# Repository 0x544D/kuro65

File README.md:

# Kuro65

The hot-swappable ISO mechanical keyboard PCB. 

Features include:
- QMK compatible
- Hot-swappable MX sockets
- 65% ISO DE layout
- Per-key RGB LED
- Multi-layer support

### Table of contents
- [Schematic](#schematic)
- [Bill of Material](#bom)
- [Pictures](#pictures)

# Schematic
<a name="schematic"/>
Standard schematic for a QMK firmware compatible mechanical keyboard.

#### Main schematic:

#### Switch matrix schematic:

# Bill of Material
<a name="bom"/>

| Qty | Component       | Footprint      | JLC Part Number | Datasheet | Shop URL                                                                 |
|-----|-----------------|----------------|-----------------|-----------|--------------------------------------------------------------------------|
|  1  | ATMEGA32U4-MU   | QFN-44_7x7x05P | C112161         |[Datasheet](https://datasheet.lcsc.com/lcsc/1809032024_Microchip-Tech-ATMEGA32U4-MU_C112161.pdf) | [Link](https://jlcpcb.com/partdetail/MicrochipTech-ATMEGA32U4MU/C112161) |
|  1  | X322516MLB4SI   | SMD3225-4P     | C13738          |[Datasheet](https://datasheet.lcsc.com/lcsc/2103291133_Yangxing-Tech-X322516MLB4SI_C13738.pdf) | [Link](https://jlcpcb.com/partdetail/YangxingTech-X322516MLB4SI/C13738) |
|  1  | B3FS-1000P      | SMD,6x6x3.1mm  | C271750         |[Datasheet](https://omronfs.omron.com/en_US/ecb/products/pdf/en-b3fs.pdf) | [Link](https://jlcpcb.com/partdetail/OmronElectronics-B3FS1000P/C271750) |
|  1  | TYPE-C-31-M-12  | SMD            | C165948         |[Datasheet](https://datasheet.lcsc.com/lcsc/2205251630_Korean-Hroparts-Elec-TYPE-C-31-M-12_C165948.pdf) | [Link](https://jlcpcb.com/partdetail/Korean_HropartsElec-TYPE_C_31_M12/C165948) |
| 70  | CPG151101S11    | SMD            | C2803348        |[Datasheet](https://datasheet.lcsc.com/lcsc/2202281830_Kailh-CPG151101S11_C2803348.pdf) | [Link](https://jlcpcb.com/partdetail/Kailh-CPG151101S11/C2803348) |
| 70  | 1N4148W         | SOD-123        | C109203         |[Datasheet](https://datasheet.lcsc.com/lcsc/1811131721_Shikues-1N4148W_C109203.pdf) | [Link](https://jlcpcb.com/partdetail/Shikues-1N4148W/C109203) |

# Pictures
<a name="pictures"/>

Kuro65 PCB

Kuro65 inside TOFU65 case

# Contributors and Acknowledgements
- Keyswitches based on: [daprice](https://github.com/daprice/keyswitches.pretty)
- Stabilizers used: [perigoso](https://github.com/perigoso/Switch_Keyboard)

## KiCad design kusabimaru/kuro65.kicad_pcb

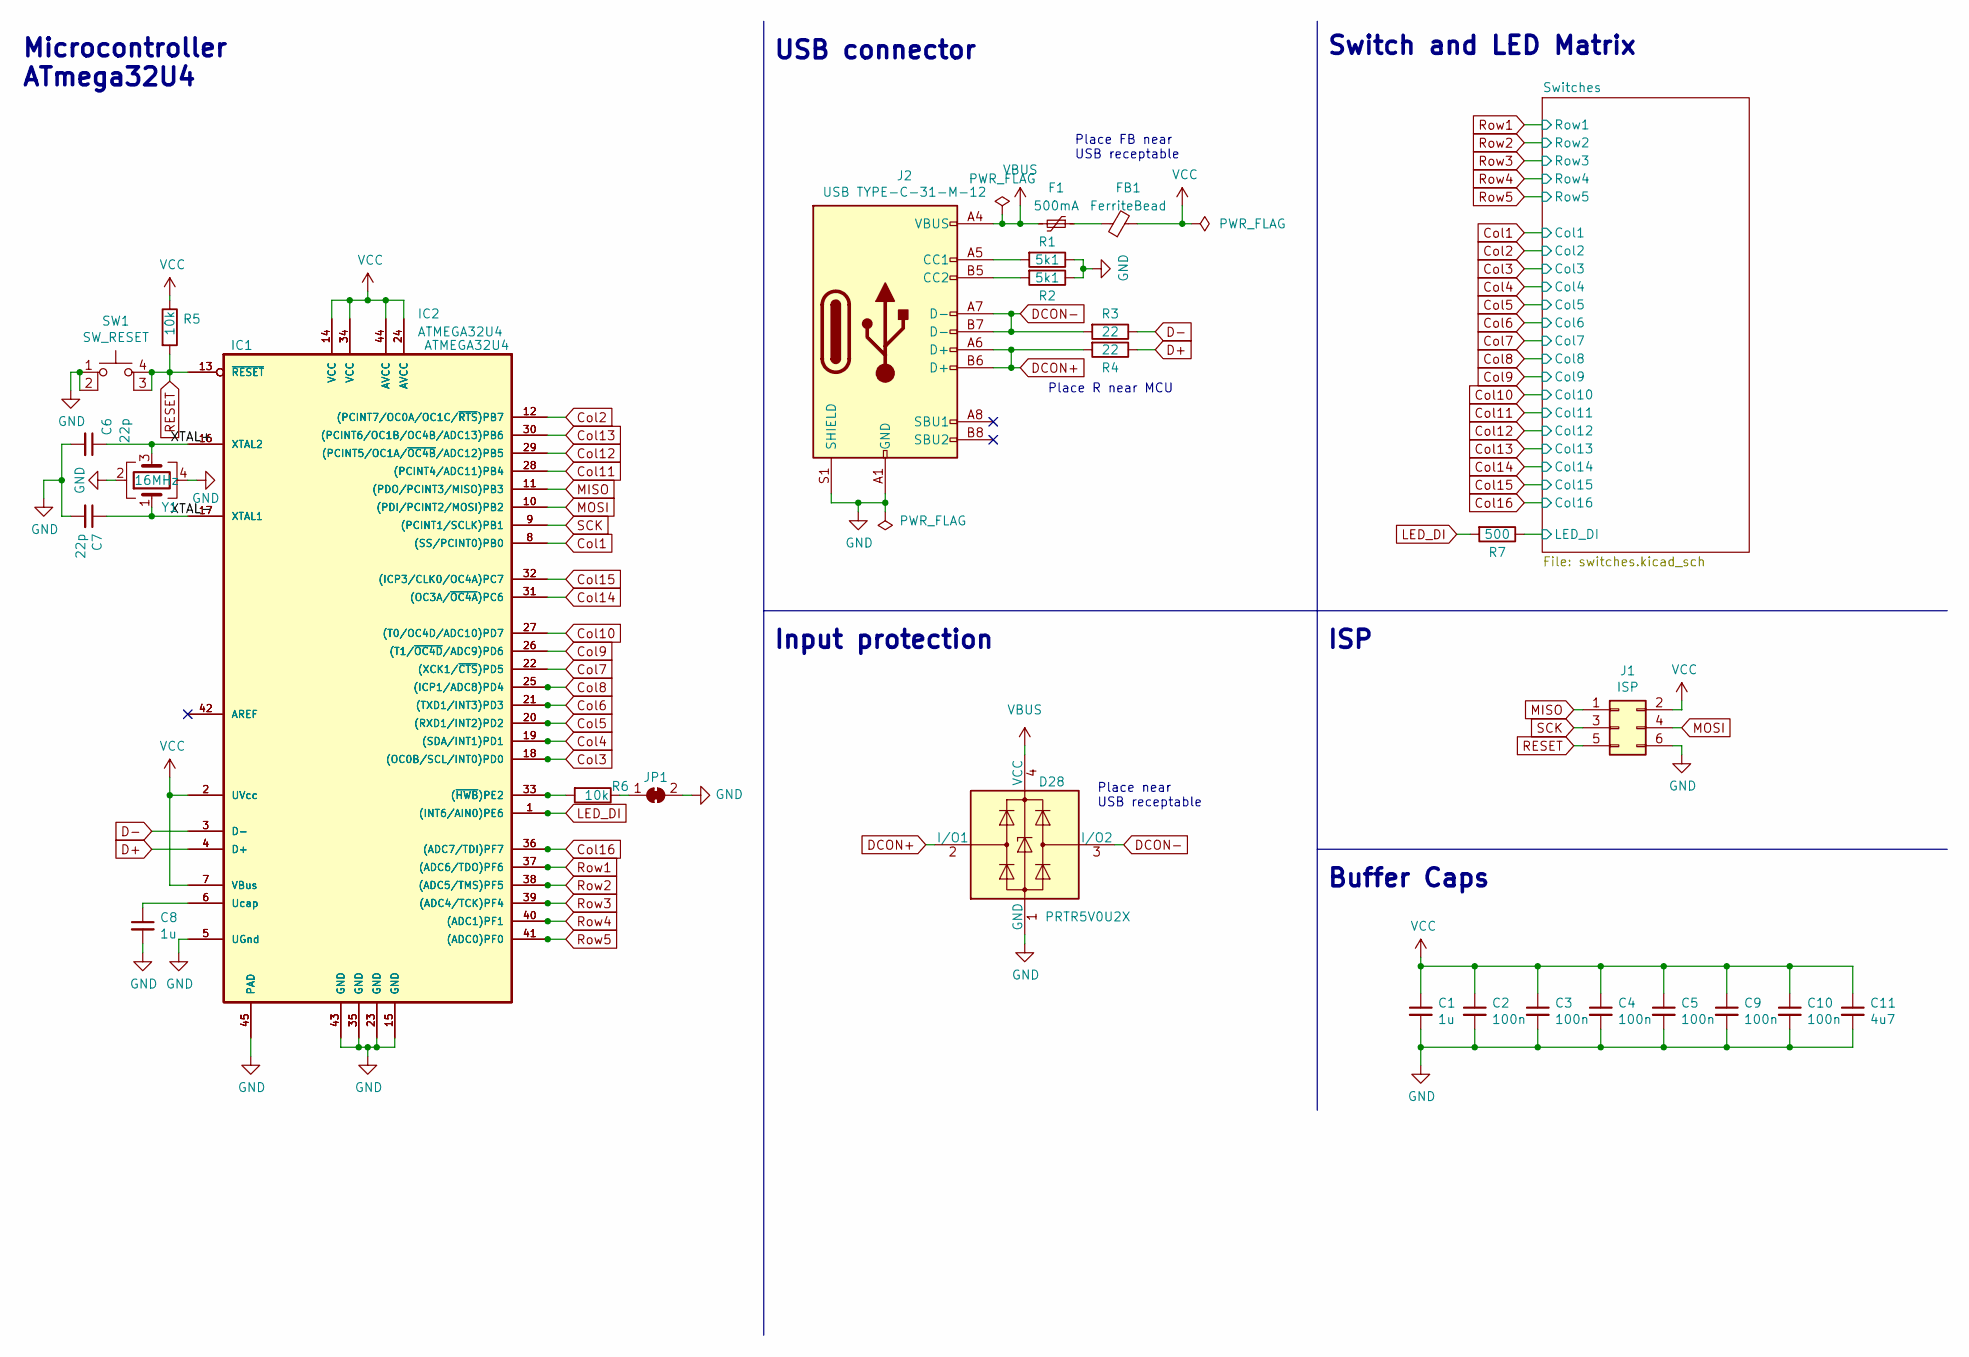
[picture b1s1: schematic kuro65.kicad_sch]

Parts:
C1, C8: 1u; C_0603_1608Metric_Pad1.08x0.95mm_HandSolder
C2, C3, C4, C5, C9, C10: 100n; C_0603_1608Metric_Pad1.08x0.95mm_HandSolder
C6, C7: 22p; C_0603_1608Metric_Pad1.08x0.95mm_HandSolder
C11: 4u7; C_0603_1608Metric_Pad1.08x0.95mm_HandSolder
D28: PRTR5V0U2X; SOT-143
F1: 500mA; Fuse_0603_1608Metric_Pad1.05x0.95mm_HandSolder
FB1: FerriteBead; R_0805_2012Metric_Pad1.20x1.40mm_HandSolder
IC1: ATMEGA32U4; QFN-44-1EP_7x7mm_P0.5mm_EP5.2x5.2mm_ThermalVias
IC2: ATMEGA32U4; LQFP-44_10x10mm_P0.8mm
J1: ISP; PinHeader_2x03_P2.54mm_Vertical
J2: USB TYPE-C-31-M-12; USB_C_Receptacle_HRO_TYPE-C-31-M-12
JP1: SolderJumper_2_Bridged; SolderJumper-2_P1.3mm_Open_Pad1.0x1.5mm
R1, R2: 5k1; R_0603_1608Metric_Pad0.98x0.95mm_HandSolder
R3, R4: 22; R_0603_1608Metric_Pad0.98x0.95mm_HandSolder
R5, R6: 10k; R_0603_1608Metric_Pad0.98x0.95mm_HandSolder
R7: 500; R_0603_1608Metric_Pad0.98x0.95mm_HandSolder
SW1: SW_RESET; SW_SPST_Omron_B3FS-100xP
Y1: 16MHz; Crystal_SMD_SeikoEpson_TSX3225-4Pin_3.2x2.5mm_HandSoldering

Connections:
/Switches/LED_DI: R7.1; also elsewhere on the board
/XTAL+: C6.1, IC1.16 (XTAL2), IC2.16 (XTAL2), Y1.3
/XTAL-: C7.1, IC1.17 (XTAL1), IC2.17 (XTAL1), Y1.1
Col1: IC1.8 ((SS/PCINT0)PB0), IC2.8 ((SS/PCINT0)PB0); also elsewhere on the board
Col2: IC1.12 ((PCINT7/OC0A/OC1C/~RTS)PB7), IC2.12 ((PCINT7/OC0A/OC1C/~RTS)PB7); also elsewhere on the board
Col3: IC1.18 ((OC0B/SCL/INT0)PD0), IC2.18 ((OC0B/SCL/INT0)PD0); also elsewhere on the board
Col4: IC1.19 ((SDA/INT1)PD1), IC2.19 ((SDA/INT1)PD1); also elsewhere on the board
Col5: IC1.20 ((RXD1/INT2)PD2), IC2.20 ((RXD1/INT2)PD2); also elsewhere on the board
Col6: IC1.21 ((TXD1/INT3)PD3), IC2.21 ((TXD1/INT3)PD3); also elsewhere on the board
Col7: IC1.22 ((XCK1/~CTS)PD5), IC2.22 ((XCK1/~CTS)PD5); also elsewhere on the board
Col8: IC1.25 ((ICP1/ADC8)PD4), IC2.25 ((ICP1/ADC8)PD4); also elsewhere on the board
Col9: IC1.26 ((T1/~OC4D/ADC9)PD6), IC2.26 ((T1/~OC4D/ADC9)PD6); also elsewhere on the board
Col10: IC1.27 ((T0/OC4D/ADC10)PD7), IC2.27 ((T0/OC4D/ADC10)PD7); also elsewhere on the board
Col11: IC1.28 ((PCINT4/ADC11)PB4), IC2.28 ((PCINT4/ADC11)PB4); also elsewhere on the board
Col12: IC1.29 ((PCINT5/OC1A/~OC4B/ADC12)PB5), IC2.29 ((PCINT5/OC1A/~OC4B/ADC12)PB5); also elsewhere on the board
Col13: IC1.30 ((PCINT6/OC1B/OC4B/ADC13)PB6), IC2.30 ((PCINT6/OC1B/OC4B/ADC13)PB6); also elsewhere on the board
Col14: IC1.31 ((OC3A/~OC4A)PC6), IC2.31 ((OC3A/~OC4A)PC6); also elsewhere on the board
Col15: IC1.32 ((ICP3/CLK0/OC4A)PC7), IC2.32 ((ICP3/CLK0/OC4A)PC7); also elsewhere on the board
Col16: IC1.36 ((ADC7/TDI)PF7), IC2.36 ((ADC7/TDI)PF7); also elsewhere on the board
D+: IC1.4 (D+), IC2.4 (D+), R4.1
D-: IC1.3 (D-), IC2.3 (D-), R3.1
DCON+: D28.2 (I/O1), J2.A6 (D+), J2.B6 (D+), R4.2
DCON-: D28.3 (I/O2), J2.A7 (D-), J2.B7 (D-), R3.2
GND: C1.2, C2.2, C3.2, C4.2, C5.2, C6.2, C7.2, C8.2, C9.2, C10.2, C11.2, D28.1 (GND), IC1.5 (UGnd), IC1.15 (GND), IC1.23 (GND), IC1.35 (GND), IC1.43 (GND), IC1.45 (PAD), IC2.5 (UGnd), IC2.15 (GND), IC2.23 (GND), IC2.35 (GND), IC2.43 (GND), IC2.45 (PAD), J1.6, J2.A1 (GND), J2.A12 (GND), J2.B1 (GND), J2.B12 (GND), J2.S1 (SHIELD), JP1.2 (B), R1.1, R2.1, SW1.1, SW1.2, Y1.2, Y1.4; also elsewhere on the board
LED_DI: IC1.1 ((INT6/AIN0)PE6), IC2.1 ((INT6/AIN0)PE6), R7.2
MISO: IC1.11 ((PDO/PCINT3/MISO)PB3), IC2.11 ((PDO/PCINT3/MISO)PB3), J1.1
MOSI: IC1.10 ((PDI/PCINT2/MOSI)PB2), IC2.10 ((PDI/PCINT2/MOSI)PB2), J1.4
unnamed: C8.1, IC1.6 (Ucap), IC2.6 (Ucap)
unnamed: F1.1, FB1.1
unnamed: IC1.33 ((~HWB)PE2), IC2.33 ((~HWB)PE2), R6.2
unnamed: J2.A5 (CC1), R1.2
unnamed: J2.B5 (CC2), R2.2
unnamed: JP1.1 (A), R6.1
RESET: IC1.13 (~RESET), IC2.13 (~RESET), J1.5, R5.2, SW1.3 (K), SW1.4 (A)
Row1: IC1.37 ((ADC6/TDO)PF6), IC2.37 ((ADC6/TDO)PF6); also elsewhere on the board
Row2: IC1.38 ((ADC5/TMS)PF5), IC2.38 ((ADC5/TMS)PF5); also elsewhere on the board
Row3: IC1.39 ((ADC4/TCK)PF4), IC2.39 ((ADC4/TCK)PF4); also elsewhere on the board
Row4: IC1.40 ((ADC1)PF1), IC2.40 ((ADC1)PF1); also elsewhere on the board
Row5: IC1.41 ((ADC0)PF0), IC2.41 ((ADC0)PF0); also elsewhere on the board
SCK: IC1.9 ((PCINT1/SCLK)PB1), IC2.9 ((PCINT1/SCLK)PB1), J1.3
VBUS: D28.4 (VCC), F1.2, J2.A4 (VBUS), J2.A9 (VBUS), J2.B4 (VBUS), J2.B9 (VBUS)
VCC: C1.1, C2.1, C3.1, C4.1, C5.1, C9.1, C10.1, C11.1, FB1.2, IC1.2 (UVcc), IC1.7 (VBus), IC1.14 (VCC), IC1.24 (AVCC), IC1.34 (VCC), IC1.44 (AVCC), IC2.2 (UVcc), IC2.7 (VBus), IC2.14 (VCC), IC2.24 (AVCC), IC2.34 (VCC), IC2.44 (AVCC), J1.2, R5.1; also elsewhere on the board

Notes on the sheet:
Buffer Caps
USB connector
Place FB near USB receptable
Input protection
Place R near MCU
ISP
Switch and LED Matrix
Place near USB receptable
Microcontroller ATmega32U4

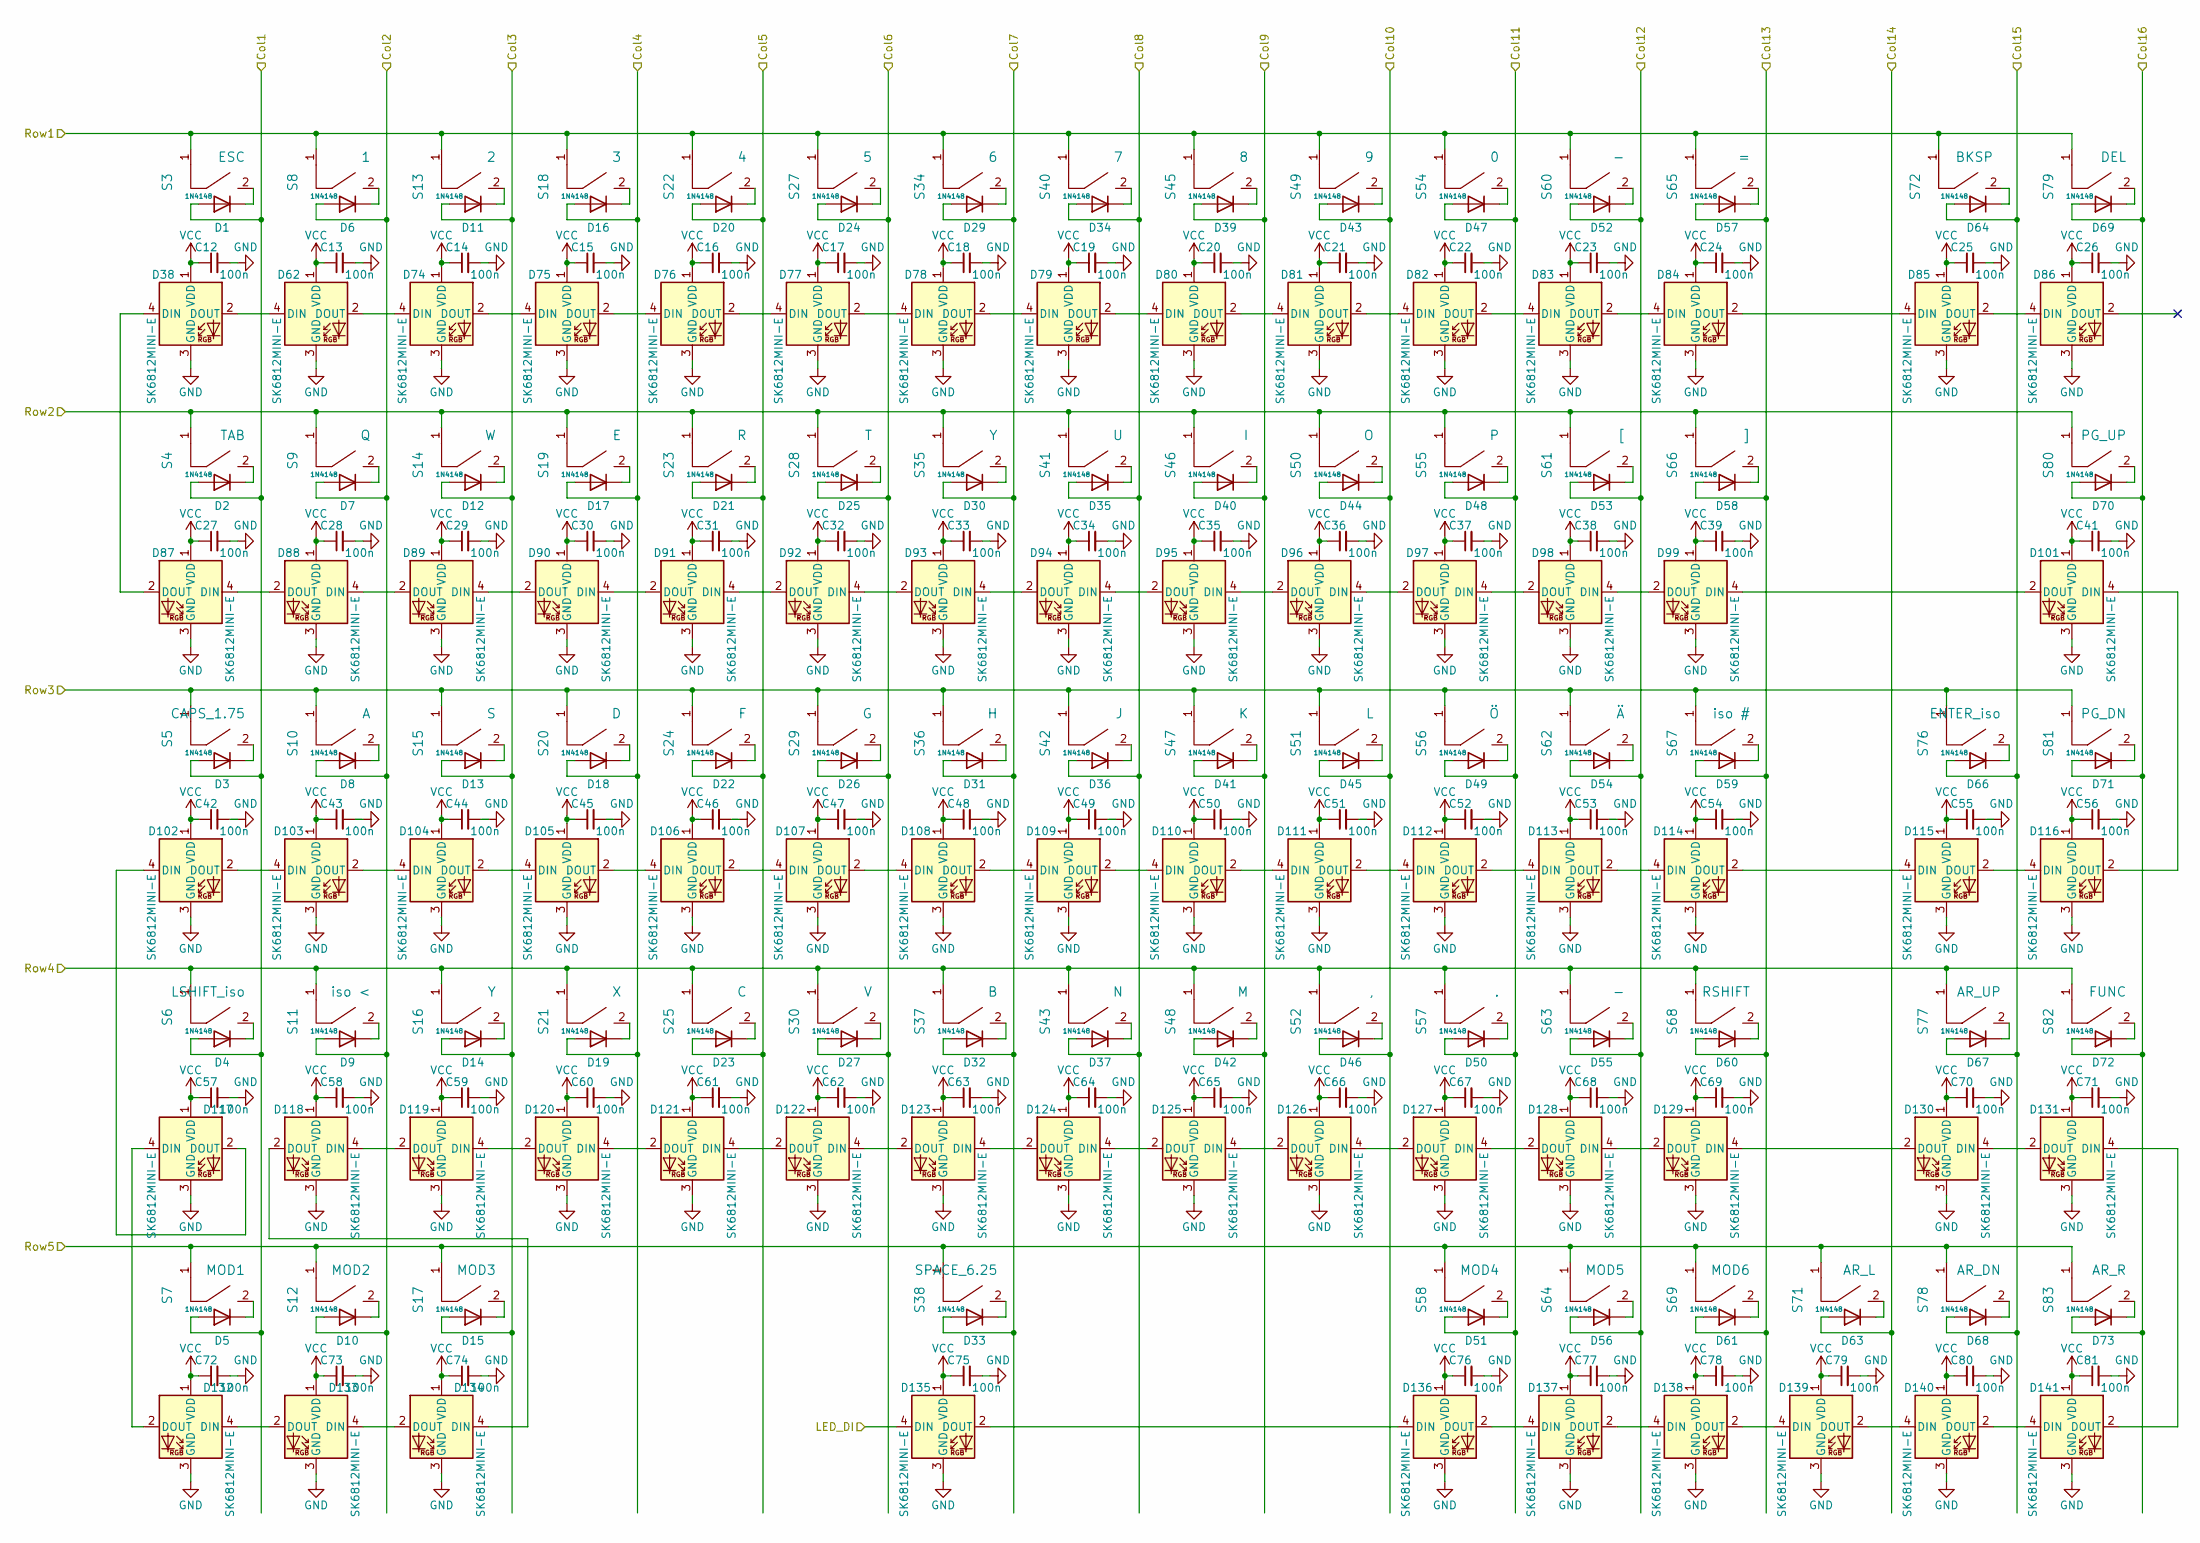
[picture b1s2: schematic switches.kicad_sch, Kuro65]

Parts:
C12, C13, C14, C15, C16, C17, C18, C19, C20, C21, C22, C23, C24, C25, C26, C27, C28, C29, C30, C31, C32, C33, C34, C35, C36, C37, C38, C39, C41, C42, C43, C44, C45, C46, C47, C48, C49, C50, C51, C52, C53, C54, C55, C56, C57, C58, C59, C60, C61, C62, C63, C64, C65, C66, C67, C68, C69, C70, C71, C72, C73, C74, C75, C76, C77, C78, C79, C80, C81: 100n; C_0603_1608Metric_Pad1.08x0.95mm_HandSolder
D1, D2, D3, D4, D5, D6, D7, D8, D9, D10, D11, D12, D13, D14, D15, D16, D17, D18, D19, D20, D21, D22, D23, D24, D25, D26, D27, D29, D30, D31, D32, D33, D34, D35, D36, D37, D39, D40, D41, D42, D43, D44, D45, D46, D47, D48, D49, D50, D51, D52, D53, D54, D55, D56, D57, D58, D59, D60, D61, D63, D64, D66, D67, D68, D69, D70, D71, D72, D73: 1N4148; D_SOD-123
D38, D62, D74, D75, D76, D77, D78, D79, D80, D81, D82, D83, D84, D85, D86, D87, D88, D89, D90, D91, D92, D93, D94, D95, D96, D97, D98, D99, D101, D102, D103, D104, D105, D106, D107, D108, D109, D110, D111, D112, D113, D114, D115, D116, D117, D118, D119, D120, D121, D122, D123, D124, D125, D126, D127, D128, D129, D130, D131, D132, D133, D134, D135, D136, D137, D138, D139, D140, D141: SK6812MINI-E; SK6812_MINI_E_small_cutout
S3: ESC; Kailh_socket_only_MX_smd_1u
S4: TAB; Kailh_socket_only_MX_smd_1.5u
S5: CAPS_1.75; Kailh_socket_only_MX_smd_1.75u
S6: LSHIFT_iso; Kailh_socket_only_MX_smd_1.25u
S7: MOD1; Kailh_socket_only_MX_smd_1.25u
S8: 1; Kailh_socket_only_MX_smd_1u
S9: Q; Kailh_socket_only_MX_smd_1u
S10: A; Kailh_socket_only_MX_smd_1u
S11: iso <; Kailh_socket_only_MX_smd_1u
S12: MOD2; Kailh_socket_only_MX_smd_1.25u
S13: 2; Kailh_socket_only_MX_smd_1u
S14: W; Kailh_socket_only_MX_smd_1u
S15: S; Kailh_socket_only_MX_smd_1u
S16, S35: Y; Kailh_socket_only_MX_smd_1u
S17: MOD3; Kailh_socket_only_MX_smd_1.25u
S18: 3; Kailh_socket_only_MX_smd_1u
S19: E; Kailh_socket_only_MX_smd_1u
S20: D; Kailh_socket_only_MX_smd_1u
S21: X; Kailh_socket_only_MX_smd_1u
S22: 4; Kailh_socket_only_MX_smd_1u
S23: R; Kailh_socket_only_MX_smd_1u
S24: F; Kailh_socket_only_MX_smd_1u
S25: C; Kailh_socket_only_MX_smd_1u
S27: 5; Kailh_socket_only_MX_smd_1u
S28: T; Kailh_socket_only_MX_smd_1u
S29: G; Kailh_socket_only_MX_smd_1u
S30: V; Kailh_socket_only_MX_smd_1u
S34: 6; Kailh_socket_only_MX_smd_1u
S36: H; Kailh_socket_only_MX_smd_1u
S37: B; Kailh_socket_only_MX_smd_1u
S38: SPACE_6.25; Kailh_socket_only_MX_smd_6.25u
S40: 7; Kailh_socket_only_MX_smd_1u
S41: U; Kailh_socket_only_MX_smd_1u
S42: J; Kailh_socket_only_MX_smd_1u
S43: N; Kailh_socket_only_MX_smd_1u
S45: 8; Kailh_socket_only_MX_smd_1u
S46: I; Kailh_socket_only_MX_smd_1u
S47: K; Kailh_socket_only_MX_smd_1u
S48: M; Kailh_socket_only_MX_smd_1u
S49: 9; Kailh_socket_only_MX_smd_1u
S50: O; Kailh_socket_only_MX_smd_1u
S51: L; Kailh_socket_only_MX_smd_1u
S52: ,; Kailh_socket_only_MX_smd_1u
S54: 0; Kailh_socket_only_MX_smd_1u
S55: P; Kailh_socket_only_MX_smd_1u
S56: Ö; Kailh_socket_only_MX_smd_1u
S57: .; Kailh_socket_only_MX_smd_1u
S58: MOD4; Kailh_socket_only_MX_smd_1u
S60, S63: -; Kailh_socket_only_MX_smd_1u
S61: [; Kailh_socket_only_MX_smd_1u
S62: Ä; Kailh_socket_only_MX_smd_1u
S64: MOD5; Kailh_socket_only_MX_smd_1u
S65: =; Kailh_socket_only_MX_smd_1u
S66: ]; Kailh_socket_only_MX_smd_1u
S67: iso #; Kailh_socket_only_MX_smd_1u
S68: RSHIFT; Kailh_socket_only_MX_smd_1.75u
S69: MOD6; Kailh_socket_only_MX_smd_1u
S71: AR_L; Kailh_socket_only_MX_smd_1u
S72: BKSP; Kailh_socket_only_MX_smd_2u
S76: ENTER_iso; Kailh_socket_only_MX_smd_iso_enter
S77: AR_UP; Kailh_socket_only_MX_smd_1u
S78: AR_DN; Kailh_socket_only_MX_smd_1u
S79: DEL; Kailh_socket_only_MX_smd_1u
S80: PG_UP; Kailh_socket_only_MX_smd_1u
S81: PG_DN; Kailh_socket_only_MX_smd_1u
S82: FUNC; Kailh_socket_only_MX_smd_1u
S83: AR_R; Kailh_socket_only_MX_smd_1u

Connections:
/Switches/LED_DI: D135.4 (DIN); also elsewhere on the board
Col1: D1.2 (A), D2.2 (A), D3.2 (A), D4.2 (A), D5.2 (A); also elsewhere on the board
Col2: D6.2 (A), D7.2 (A), D8.2 (A), D9.2 (A), D10.2 (A); also elsewhere on the board
Col3: D11.2 (A), D12.2 (A), D13.2 (A), D14.2 (A), D15.2 (A); also elsewhere on the board
Col4: D16.2 (A), D17.2 (A), D18.2 (A), D19.2 (A); also elsewhere on the board
Col5: D20.2 (A), D21.2 (A), D22.2 (A), D23.2 (A); also elsewhere on the board
Col6: D24.2 (A), D25.2 (A), D26.2 (A), D27.2 (A); also elsewhere on the board
Col7: D29.2 (A), D30.2 (A), D31.2 (A), D32.2 (A), D33.2 (A); also elsewhere on the board
Col8: D34.2 (A), D35.2 (A), D36.2 (A), D37.2 (A); also elsewhere on the board
Col9: D39.2 (A), D40.2 (A), D41.2 (A), D42.2 (A); also elsewhere on the board
Col10: D43.2 (A), D44.2 (A), D45.2 (A), D46.2 (A); also elsewhere on the board
Col11: D47.2 (A), D48.2 (A), D49.2 (A), D50.2 (A), D51.2 (A); also elsewhere on the board
Col12: D52.2 (A), D53.2 (A), D54.2 (A), D55.2 (A), D56.2 (A); also elsewhere on the board
Col13: D57.2 (A), D58.2 (A), D59.2 (A), D60.2 (A), D61.2 (A); also elsewhere on the board
Col14: D63.2 (A); also elsewhere on the board
Col15: D64.2 (A), D66.2 (A), D67.2 (A), D68.2 (A); also elsewhere on the board
Col16: D69.2 (A), D70.2 (A), D71.2 (A), D72.2 (A), D73.2 (A); also elsewhere on the board
GND: C12.2, C13.2, C14.2, C15.2, C16.2, C17.2, C18.2, C19.2, C20.2, C21.2, C22.2, C23.2, C24.2, C25.2, C26.2, C27.2, C28.2, C29.2, C30.2, C31.2, C32.2, C33.2, C34.2, C35.2, C36.2, C37.2, C38.2, C39.2, C41.2, C42.2, C43.2, C44.2, C45.2, C46.2, C47.2, C48.2, C49.2, C50.2, C51.2, C52.2, C53.2, C54.2, C55.2, C56.2, C57.2, C58.2, C59.2, C60.2, C61.2, C62.2, C63.2, C64.2, C65.2, C66.2, C67.2, C68.2, C69.2, C70.2, C71.2, C72.2, C73.2, C74.2, C75.2, C76.2, C77.2, C78.2, C79.2, C80.2, C81.2, D38.3 (GND), D62.3 (GND), D74.3 (GND), D75.3 (GND), D76.3 (GND), D77.3 (GND), D78.3 (GND), D79.3 (GND), D80.3 (GND), D81.3 (GND), D82.3 (GND), D83.3 (GND), D84.3 (GND), D85.3 (GND), D86.3 (GND), D87.3 (GND), D88.3 (GND), D89.3 (GND), D90.3 (GND), D91.3 (GND), D92.3 (GND), D93.3 (GND), D94.3 (GND), D95.3 (GND), D96.3 (GND), D97.3 (GND), D98.3 (GND), D99.3 (GND), D101.3 (GND), D102.3 (GND), D103.3 (GND), D104.3 (GND), D105.3 (GND), D106.3 (GND), D107.3 (GND), D108.3 (GND), D109.3 (GND), D110.3 (GND), D111.3 (GND), D112.3 (GND), D113.3 (GND), D114.3 (GND), D115.3 (GND), D116.3 (GND), D117.3 (GND), D118.3 (GND), D119.3 (GND), D120.3 (GND), D121.3 (GND), D122.3 (GND), D123.3 (GND), D124.3 (GND), D125.3 (GND), D126.3 (GND), D127.3 (GND), D128.3 (GND), D129.3 (GND), D130.3 (GND), D131.3 (GND), D132.3 (GND), D133.3 (GND), D134.3 (GND), D135.3 (GND), D136.3 (GND), D137.3 (GND), D138.3 (GND), D139.3 (GND), D140.3 (GND), D141.3 (GND); also elsewhere on the board
unnamed: D1.1 (K), S3.2
unnamed: D2.1 (K), S4.2
unnamed: D3.1 (K), S5.2
unnamed: D4.1 (K), S6.2
unnamed: D5.1 (K), S7.2
unnamed: D6.1 (K), S8.2
unnamed: D7.1 (K), S9.2
unnamed: D8.1 (K), S10.2
unnamed: D9.1 (K), S11.2
unnamed: D10.1 (K), S12.2
unnamed: D11.1 (K), S13.2
unnamed: D12.1 (K), S14.2
unnamed: D13.1 (K), S15.2
unnamed: D14.1 (K), S16.2
unnamed: D15.1 (K), S17.2
unnamed: D16.1 (K), S18.2
unnamed: D17.1 (K), S19.2
unnamed: D18.1 (K), S20.2
unnamed: D19.1 (K), S21.2
unnamed: D20.1 (K), S22.2
unnamed: D21.1 (K), S23.2
unnamed: D22.1 (K), S24.2
unnamed: D23.1 (K), S25.2
unnamed: D24.1 (K), S27.2
unnamed: D25.1 (K), S28.2
unnamed: D26.1 (K), S29.2
unnamed: D27.1 (K), S30.2
unnamed: D29.1 (K), S34.2
unnamed: D30.1 (K), S35.2
unnamed: D31.1 (K), S36.2
unnamed: D32.1 (K), S37.2
unnamed: D33.1 (K), S38.2
unnamed: D34.1 (K), S40.2
unnamed: D35.1 (K), S41.2
unnamed: D36.1 (K), S42.2
unnamed: D37.1 (K), S43.2
unnamed: D38.2 (DOUT), D62.4 (DIN)
unnamed: D39.1 (K), S45.2
unnamed: D40.1 (K), S46.2
unnamed: D41.1 (K), S47.2
unnamed: D42.1 (K), S48.2
unnamed: D43.1 (K), S49.2
unnamed: D44.1 (K), S50.2
unnamed: D45.1 (K), S51.2
unnamed: D46.1 (K), S52.2
unnamed: D47.1 (K), S54.2
unnamed: D48.1 (K), S55.2
unnamed: D49.1 (K), S56.2
unnamed: D50.1 (K), S57.2
unnamed: D51.1 (K), S58.2
unnamed: D52.1 (K), S60.2
unnamed: D53.1 (K), S61.2
unnamed: D54.1 (K), S62.2
unnamed: D55.1 (K), S63.2
unnamed: D56.1 (K), S64.2
unnamed: D57.1 (K), S65.2
unnamed: D58.1 (K), S66.2
unnamed: D59.1 (K), S67.2
unnamed: D60.1 (K), S68.2
unnamed: D61.1 (K), S69.2
unnamed: D62.2 (DOUT), D74.4 (DIN)
unnamed: D63.1 (K), S71.2
unnamed: D64.1 (K), S72.2
unnamed: D66.1 (K), S76.2
unnamed: D67.1 (K), S77.2
unnamed: D68.1 (K), S78.2
unnamed: D69.1 (K), S79.2
unnamed: D70.1 (K), S80.2
unnamed: D71.1 (K), S81.2
unnamed: D72.1 (K), S82.2
unnamed: D73.1 (K), S83.2
unnamed: D74.2 (DOUT), D75.4 (DIN)
unnamed: D75.2 (DOUT), D76.4 (DIN)
unnamed: D76.2 (DOUT), D77.4 (DIN)
unnamed: D77.2 (DOUT), D78.4 (DIN)
unnamed: D78.2 (DOUT), D79.4 (DIN)
unnamed: D79.2 (DOUT), D80.4 (DIN)
unnamed: D80.2 (DOUT), D81.4 (DIN)
unnamed: D81.2 (DOUT), D82.4 (DIN)
unnamed: D82.2 (DOUT), D83.4 (DIN)
unnamed: D83.2 (DOUT), D84.4 (DIN)
unnamed: D84.2 (DOUT), D85.4 (DIN)
unnamed: D85.2 (DOUT), D86.4 (DIN)
unnamed: D38.4 (DIN), D87.2 (DOUT)
unnamed: D87.4 (DIN), D88.2 (DOUT)
unnamed: D88.4 (DIN), D89.2 (DOUT)
unnamed: D89.4 (DIN), D90.2 (DOUT)
unnamed: D90.4 (DIN), D91.2 (DOUT)
unnamed: D91.4 (DIN), D92.2 (DOUT)
unnamed: D92.4 (DIN), D93.2 (DOUT)
unnamed: D93.4 (DIN), D94.2 (DOUT)
unnamed: D94.4 (DIN), D95.2 (DOUT)
unnamed: D95.4 (DIN), D96.2 (DOUT)
unnamed: D96.4 (DIN), D97.2 (DOUT)
unnamed: D97.4 (DIN), D98.2 (DOUT)
unnamed: D98.4 (DIN), D99.2 (DOUT)
unnamed: D99.4 (DIN), D101.2 (DOUT)
unnamed: D102.2 (DOUT), D103.4 (DIN)
unnamed: D102.4 (DIN), D117.2 (DOUT)
unnamed: D103.2 (DOUT), D104.4 (DIN)
unnamed: D104.2 (DOUT), D105.4 (DIN)
unnamed: D105.2 (DOUT), D106.4 (DIN)
unnamed: D106.2 (DOUT), D107.4 (DIN)
unnamed: D107.2 (DOUT), D108.4 (DIN)
unnamed: D108.2 (DOUT), D109.4 (DIN)
unnamed: D109.2 (DOUT), D110.4 (DIN)
unnamed: D110.2 (DOUT), D111.4 (DIN)
unnamed: D111.2 (DOUT), D112.4 (DIN)
unnamed: D112.2 (DOUT), D113.4 (DIN)
unnamed: D113.2 (DOUT), D114.4 (DIN)
unnamed: D114.2 (DOUT), D115.4 (DIN)
unnamed: D115.2 (DOUT), D116.4 (DIN)
unnamed: D101.4 (DIN), D116.2 (DOUT)
unnamed: D117.4 (DIN), D132.2 (DOUT)
unnamed: D118.2 (DOUT), D134.4 (DIN)
unnamed: D118.4 (DIN), D119.2 (DOUT)
unnamed: D119.4 (DIN), D120.2 (DOUT)
unnamed: D120.4 (DIN), D121.2 (DOUT)
unnamed: D121.4 (DIN), D122.2 (DOUT)
unnamed: D122.4 (DIN), D123.2 (DOUT)
unnamed: D123.4 (DIN), D124.2 (DOUT)
unnamed: D124.4 (DIN), D125.2 (DOUT)
unnamed: D125.4 (DIN), D126.2 (DOUT)
unnamed: D126.4 (DIN), D127.2 (DOUT)
unnamed: D127.4 (DIN), D128.2 (DOUT)
unnamed: D128.4 (DIN), D129.2 (DOUT)
unnamed: D129.4 (DIN), D130.2 (DOUT)
unnamed: D130.4 (DIN), D131.2 (DOUT)
unnamed: D131.4 (DIN), D141.2 (DOUT)
unnamed: D132.4 (DIN), D133.2 (DOUT)
unnamed: D133.4 (DIN), D134.2 (DOUT)
unnamed: D135.2 (DOUT), D136.4 (DIN)
unnamed: D136.2 (DOUT), D137.4 (DIN)
unnamed: D137.2 (DOUT), D138.4 (DIN)
unnamed: D138.2 (DOUT), D139.4 (DIN)
unnamed: D139.2 (DOUT), D140.4 (DIN)
unnamed: D140.2 (DOUT), D141.4 (DIN)
Row1: S3.1, S8.1, S13.1, S18.1, S22.1, S27.1, S34.1, S40.1, S45.1, S49.1, S54.1, S60.1, S65.1, S72.1, S79.1; also elsewhere on the board
Row2: S4.1, S9.1, S14.1, S19.1, S23.1, S28.1, S35.1, S41.1, S46.1, S50.1, S55.1, S61.1, S66.1, S80.1; also elsewhere on the board
Row3: S5.1, S10.1, S15.1, S20.1, S24.1, S29.1, S36.1, S42.1, S47.1, S51.1, S56.1, S62.1, S67.1, S76.1, S81.1; also elsewhere on the board
Row4: S6.1, S11.1, S16.1, S21.1, S25.1, S30.1, S37.1, S43.1, S48.1, S52.1, S57.1, S63.1, S68.1, S77.1, S82.1; also elsewhere on the board
Row5: S7.1, S12.1, S17.1, S38.1, S58.1, S64.1, S69.1, S71.1, S78.1, S83.1; also elsewhere on the board
VCC: C12.1, C13.1, C14.1, C15.1, C16.1, C17.1, C18.1, C19.1, C20.1, C21.1, C22.1, C23.1, C24.1, C25.1, C26.1, C27.1, C28.1, C29.1, C30.1, C31.1, C32.1, C33.1, C34.1, C35.1, C36.1, C37.1, C38.1, C39.1, C41.1, C42.1, C43.1, C44.1, C45.1, C46.1, C47.1, C48.1, C49.1, C50.1, C51.1, C52.1, C53.1, C54.1, C55.1, C56.1, C57.1, C58.1, C59.1, C60.1, C61.1, C62.1, C63.1, C64.1, C65.1, C66.1, C67.1, C68.1, C69.1, C70.1, C71.1, C72.1, C73.1, C74.1, C75.1, C76.1, C77.1, C78.1, C79.1, C80.1, C81.1, D38.1 (VDD), D62.1 (VDD), D74.1 (VDD), D75.1 (VDD), D76.1 (VDD), D77.1 (VDD), D78.1 (VDD), D79.1 (VDD), D80.1 (VDD), D81.1 (VDD), D82.1 (VDD), D83.1 (VDD), D84.1 (VDD), D85.1 (VDD), D86.1 (VDD), D87.1 (VDD), D88.1 (VDD), D89.1 (VDD), D90.1 (VDD), D91.1 (VDD), D92.1 (VDD), D93.1 (VDD), D94.1 (VDD), D95.1 (VDD), D96.1 (VDD), D97.1 (VDD), D98.1 (VDD), D99.1 (VDD), D101.1 (VDD), D102.1 (VDD), D103.1 (VDD), D104.1 (VDD), D105.1 (VDD), D106.1 (VDD), D107.1 (VDD), D108.1 (VDD), D109.1 (VDD), D110.1 (VDD), D111.1 (VDD), D112.1 (VDD), D113.1 (VDD), D114.1 (VDD), D115.1 (VDD), D116.1 (VDD), D117.1 (VDD), D118.1 (VDD), D119.1 (VDD), D120.1 (VDD), D121.1 (VDD), D122.1 (VDD), D123.1 (VDD), D124.1 (VDD), D125.1 (VDD), D126.1 (VDD), D127.1 (VDD), D128.1 (VDD), D129.1 (VDD), D130.1 (VDD), D131.1 (VDD), D132.1 (VDD), D133.1 (VDD), D134.1 (VDD), D135.1 (VDD), D136.1 (VDD), D137.1 (VDD), D138.1 (VDD), D139.1 (VDD), D140.1 (VDD), D141.1 (VDD); also elsewhere on the board

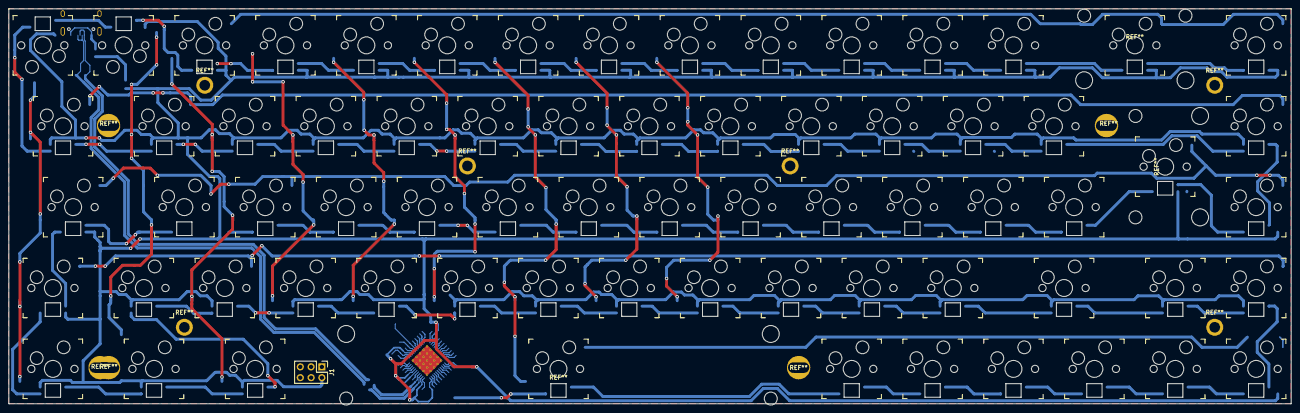
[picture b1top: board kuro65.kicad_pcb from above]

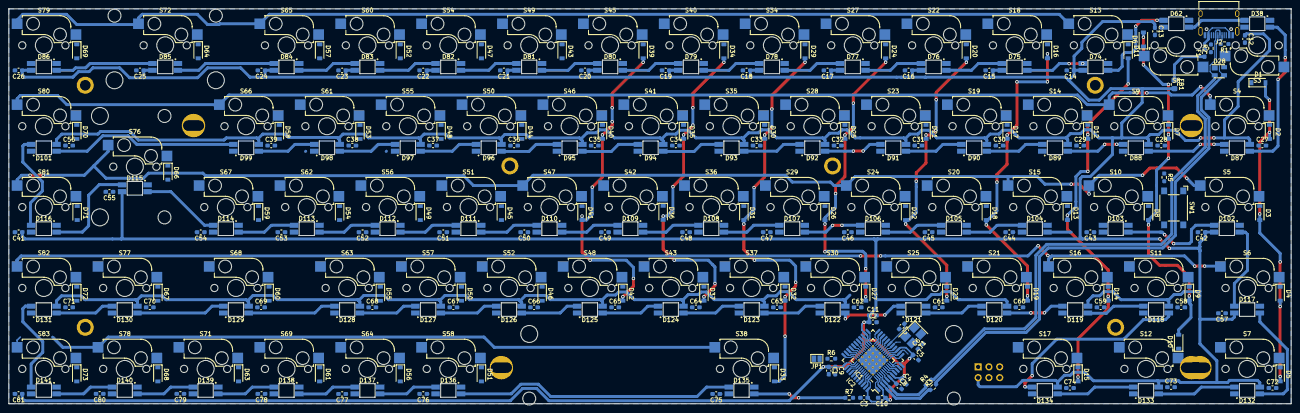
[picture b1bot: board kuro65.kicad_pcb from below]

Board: 2 copper layers, 302.0 x 93.0 mm, 304 parts (165 on the bottom side), 179 nets.

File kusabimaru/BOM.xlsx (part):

Source: | C:\Users\Tobi\Documents\GitHub\kuro65\kusabimaru\kuro65.sch
Date: | 44240.65384259259
Tool: | Eeschema (5.1.9)-1
Generator: | C:\Program Files\KiCad\bin\scripting\plugins/bom_csv_grouped_by_value.py
Component Count: | 171
Individual Components:
Item | Qty | Reference(s) | Value | LibPart | Footprint | Datasheet | Shop-URL
 |  | C1 | 1u | Device:C_Small | Capacitor_SMD:C_0805_2012Metric_Pad1.18x1.45mm_HandSolder | ~
 |  | C2 | 100n | Device:C_Small | Capacitor_SMD:C_0805_2012Metric_Pad1.18x1.45mm_HandSolder | ~
 |  | C3 | 100n | Device:C_Small | Capacitor_SMD:C_0805_2012Metric_Pad1.18x1.45mm_HandSolder | ~
 |  | C4 | 100n | Device:C_Small | Capacitor_SMD:C_0805_2012Metric_Pad1.18x1.45mm_HandSolder | ~
 |  | C5 | 100n | Device:C_Small | Capacitor_SMD:C_0805_2012Metric_Pad1.18x1.45mm_HandSolder | ~
 |  | C6 | 22p | Device:C_Small | Capacitor_SMD:C_0805_2012Metric_Pad1.18x1.45mm_HandSolder | ~
 |  | C7 | 22p | Device:C_Small | Capacitor_SMD:C_0805_2012Metric_Pad1.18x1.45mm_HandSolder | ~
 |  | C8 | 1u | Device:C_Small | Capacitor_SMD:C_0805_2012Metric_Pad1.18x1.45mm_HandSolder | ~
 |  | C9 | 100n | Device:C_Small | Capacitor_SMD:C_0805_2012Metric_Pad1.18x1.45mm_HandSolder | ~
 |  | C10 | 100n | Device:C_Small | Capacitor_SMD:C_0805_2012Metric_Pad1.18x1.45mm_HandSolder | ~
 |  | C11 | 4u7 | Device:C_Small | Capacitor_SMD:C_0805_2012Metric_Pad1.18x1.45mm_HandSolder | ~
 |  | D1 | 1N4148 | Device:D | Diode_SMD:D_0805_2012Metric_Pad1.15x1.40mm_HandSolder | ~
 |  | D2 | 1N4148 | Device:D | Diode_SMD:D_0805_2012Metric_Pad1.15x1.40mm_HandSolder | ~
 |  | D3 | 1N4148 | Device:D | Diode_SMD:D_0805_2012Metric_Pad1.15x1.40mm_HandSolder | ~
 |  | D4 | 1N4148 | Device:D | Diode_SMD:D_0805_2012Metric_Pad1.15x1.40mm_HandSolder | ~
 |  | D5 | 1N4148 | Device:D | Diode_SMD:D_0805_2012Metric_Pad1.15x1.40mm_HandSolder | ~
 |  | D6 | 1N4148 | Device:D | Diode_SMD:D_0805_2012Metric_Pad1.15x1.40mm_HandSolder | ~
 |  | D7 | 1N4148 | Device:D | Diode_SMD:D_0805_2012Metric_Pad1.15x1.40mm_HandSolder | ~
 |  | D8 | 1N4148 | Device:D | Diode_SMD:D_0805_2012Metric_Pad1.15x1.40mm_HandSolder | ~
 |  | D9 | 1N4148 | Device:D | Diode_SMD:D_0805_2012Metric_Pad1.15x1.40mm_HandSolder | ~
 |  | D10 | 1N4148 | Device:D | Diode_SMD:D_0805_2012Metric_Pad1.15x1.40mm_HandSolder | ~
 |  | D11 | 1N4148 | Device:D | Diode_SMD:D_0805_2012Metric_Pad1.15x1.40mm_HandSolder | ~
 |  | D12 | 1N4148 | Device:D | Diode_SMD:D_0805_2012Metric_Pad1.15x1.40mm_HandSolder | ~
 |  | D13 | 1N4148 | Device:D | Diode_SMD:D_0805_2012Metric_Pad1.15x1.40mm_HandSolder | ~
 |  | D14 | 1N4148 | Device:D | Diode_SMD:D_0805_2012Metric_Pad1.15x1.40mm_HandSolder | ~
 |  | D15 | 1N4148 | Device:D | Diode_SMD:D_0805_2012Metric_Pad1.15x1.40mm_HandSolder | ~
 |  | D16 | 1N4148 | Device:D | Diode_SMD:D_0805_2012Metric_Pad1.15x1.40mm_HandSolder | ~
 |  | D17 | 1N4148 | Device:D | Diode_SMD:D_0805_2012Metric_Pad1.15x1.40mm_HandSolder | ~
 |  | D18 | 1N4148 | Device:D | Diode_SMD:D_0805_2012Metric_Pad1.15x1.40mm_HandSolder | ~
 |  | D19 | 1N4148 | Device:D | Diode_SMD:D_0805_2012Metric_Pad1.15x1.40mm_HandSolder | ~
 |  | D20 | 1N4148 | Device:D | Diode_SMD:D_0805_2012Metric_Pad1.15x1.40mm_HandSolder | ~
 |  | D21 | 1N4148 | Device:D | Diode_SMD:D_0805_2012Metric_Pad1.15x1.40mm_HandSolder | ~
 |  | D22 | 1N4148 | Device:D | Diode_SMD:D_0805_2012Metric_Pad1.15x1.40mm_HandSolder | ~
 |  | D23 | 1N4148 | Device:D | Diode_SMD:D_0805_2012Metric_Pad1.15x1.40mm_HandSolder | ~
 |  | D24 | 1N4148 | Device:D | Diode_SMD:D_0805_2012Metric_Pad1.15x1.40mm_HandSolder | ~
 |  | D25 | 1N4148 | Device:D | Diode_SMD:D_0805_2012Metric_Pad1.15x1.40mm_HandSolder | ~
 |  | D26 | 1N4148 | Device:D | Diode_SMD:D_0805_2012Metric_Pad1.15x1.40mm_HandSolder | ~
 |  | D27 | 1N4148 | Device:D | Diode_SMD:D_0805_2012Metric_Pad1.15x1.40mm_HandSolder | ~
 |  | D29 | 1N4148 | Device:D | Diode_SMD:D_0805_2012Metric_Pad1.15x1.40mm_HandSolder | ~
 |  | D30 | 1N4148 | Device:D | Diode_SMD:D_0805_2012Metric_Pad1.15x1.40mm_HandSolder | ~
 |  | D31 | 1N4148 | Device:D | Diode_SMD:D_0805_2012Metric_Pad1.15x1.40mm_HandSolder | ~
 |  | D32 | 1N4148 | Device:D | Diode_SMD:D_0805_2012Metric_Pad1.15x1.40mm_HandSolder | ~
 |  | D33 | 1N4148 | Device:D | Diode_SMD:D_0805_2012Metric_Pad1.15x1.40mm_HandSolder | ~
 |  | D34 | 1N4148 | Device:D | Diode_SMD:D_0805_2012Metric_Pad1.15x1.40mm_HandSolder | ~
 |  | D35 | 1N4148 | Device:D | Diode_SMD:D_0805_2012Metric_Pad1.15x1.40mm_HandSolder | ~
 |  | D36 | 1N4148 | Device:D | Diode_SMD:D_0805_2012Metric_Pad1.15x1.40mm_HandSolder | ~
 |  | D37 | 1N4148 | Device:D | Diode_SMD:D_0805_2012Metric_Pad1.15x1.40mm_HandSolder | ~
 |  | D39 | 1N4148 | Device:D | Diode_SMD:D_0805_2012Metric_Pad1.15x1.40mm_HandSolder | ~
 |  | D40 | 1N4148 | Device:D | Diode_SMD:D_0805_2012Metric_Pad1.15x1.40mm_HandSolder | ~
 |  | D41 | 1N4148 | Device:D | Diode_SMD:D_0805_2012Metric_Pad1.15x1.40mm_HandSolder | ~
 |  | D42 | 1N4148 | Device:D | Diode_SMD:D_0805_2012Metric_Pad1.15x1.40mm_HandSolder | ~
 |  | D43 | 1N4148 | Device:D | Diode_SMD:D_0805_2012Metric_Pad1.15x1.40mm_HandSolder | ~
 |  | D44 | 1N4148 | Device:D | Diode_SMD:D_0805_2012Metric_Pad1.15x1.40mm_HandSolder | ~
 |  | D45 | 1N4148 | Device:D | Diode_SMD:D_0805_2012Metric_Pad1.15x1.40mm_HandSolder | ~
 |  | D46 | 1N4148 | Device:D | Diode_SMD:D_0805_2012Metric_Pad1.15x1.40mm_HandSolder | ~
 |  | D47 | 1N4148 | Device:D | Diode_SMD:D_0805_2012Metric_Pad1.15x1.40mm_HandSolder | ~
 |  | D48 | 1N4148 | Device:D | Diode_SMD:D_0805_2012Metric_Pad1.15x1.40mm_HandSolder | ~
 |  | D49 | 1N4148 | Device:D | Diode_SMD:D_0805_2012Metric_Pad1.15x1.40mm_HandSolder | ~
 |  | D50 | 1N4148 | Device:D | Diode_SMD:D_0805_2012Metric_Pad1.15x1.40mm_HandSolder | ~
 |  | D51 | 1N4148 | Device:D | Diode_SMD:D_0805_2012Metric_Pad1.15x1.40mm_HandSolder | ~
 |  | D52 | 1N4148 | Device:D | Diode_SMD:D_0805_2012Metric_Pad1.15x1.40mm_HandSolder | ~
 |  | D53 | 1N4148 | Device:D | Diode_SMD:D_0805_2012Metric_Pad1.15x1.40mm_HandSolder | ~
 |  | D54 | 1N4148 | Device:D | Diode_SMD:D_0805_2012Metric_Pad1.15x1.40mm_HandSolder | ~
 |  | D55 | 1N4148 | Device:D | Diode_SMD:D_0805_2012Metric_Pad1.15x1.40mm_HandSolder | ~
 |  | D56 | 1N4148 | Device:D | Diode_SMD:D_0805_2012Metric_Pad1.15x1.40mm_HandSolder | ~
 |  | D57 | 1N4148 | Device:D | Diode_SMD:D_0805_2012Metric_Pad1.15x1.40mm_HandSolder | ~
 |  | D58 | 1N4148 | Device:D | Diode_SMD:D_0805_2012Metric_Pad1.15x1.40mm_HandSolder | ~
 |  | D59 | 1N4148 | Device:D | Diode_SMD:D_0805_2012Metric_Pad1.15x1.40mm_HandSolder | ~
 |  | D60 | 1N4148 | Device:D | Diode_SMD:D_0805_2012Metric_Pad1.15x1.40mm_HandSolder | ~
 |  | D61 | 1N4148 | Device:D | Diode_SMD:D_0805_2012Metric_Pad1.15x1.40mm_HandSolder | ~
 |  | D62 | 1N4148 | Device:D | Diode_SMD:D_0805_2012Metric_Pad1.15x1.40mm_HandSolder | ~
 |  | D63 | 1N4148 | Device:D | Diode_SMD:D_0805_2012Metric_Pad1.15x1.40mm_HandSolder | ~
 |  | D64 | 1N4148 | Device:D | Diode_SMD:D_0805_2012Metric_Pad1.15x1.40mm_HandSolder | ~
 |  | D65 | 1N4148 | Device:D | Diode_SMD:D_0805_2012Metric_Pad1.15x1.40mm_HandSolder | ~
 |  | D66 | 1N4148 | Device:D | Diode_SMD:D_0805_2012Metric_Pad1.15x1.40mm_HandSolder | ~
 |  | D67 | 1N4148 | Device:D | Diode_SMD:D_0805_2012Metric_Pad1.15x1.40mm_HandSolder | ~
 |  | D68 | 1N4148 | Device:D | Diode_SMD:D_0805_2012Metric_Pad1.15x1.40mm_HandSolder | ~
 |  | D69 | 1N4148 | Device:D | Diode_SMD:D_0805_2012Metric_Pad1.15x1.40mm_HandSolder | ~
 |  | D70 | 1N4148 | Device:D | Diode_SMD:D_0805_2012Metric_Pad1.15x1.40mm_HandSolder | ~
 |  | D71 | 1N4148 | Device:D | Diode_SMD:D_0805_2012Metric_Pad1.15x1.40mm_HandSolder | ~
 |  | D72 | 1N4148 | Device:D | Diode_SMD:D_0805_2012Metric_Pad1.15x1.40mm_HandSolder | ~
 |  | D73 | 1N4148 | Device:D | Diode_SMD:D_0805_2012Metric_Pad1.15x1.40mm_HandSolder | ~
 |  | IC1 | ATMEGA32U4 | atmega32u4:ATMEGA32U4 | Package_QFP:TQFP-44_10x10mm_P0.8mm
 |  | J1 | ISP | Connector_Generic:Conn_02x03_Odd_Even | Connector_PinHeader_2.54mm:PinHeader_2x03_P2.54mm_Vertical | ~
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
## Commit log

2021-02-06 Initial commit of existing files
2021-02-06 Added credits and acknowledgements
2021-02-06 Initial component placement done
2021-02-11 Some routing done + References added
2021-02-12 Routing completed. Some modifications still needed.
2021-02-12 Added logo to project and placed on PCB.
2021-02-13 Some PCB adjustments.
2021-02-13 Updated README with BOM
2021-02-14 Updated README: Supplied links to components
2021-02-14 Exchanged diode footpint to SOD-323
2021-02-14 Added datasheets to README.md
2021-02-14 Fixed typos in README
2021-02-14 Added additional logos and some 3D render pictures
2021-02-14 Added pictures to README file
2021-02-20 Added schematic pictures
2021-02-20 Updated README and added schematic pictures.
2021-02-21 Added table of contents
2022-08-14 Exchanged old lib folder with kicad_lib repo. Upgraded Kicad files to version 6.
2022-08-14 Updated kicad_lib to most recent version.
2022-08-14 Changed schematic and PCB layout for kuro65. Routing of PCB is incomplete.
2022-08-14 Update kicad_libs pointer.
2022-08-14 Updates on PCB layout. Placement of LED components corrected.
2022-11-17 Added Tofu65 dimension reference.
2022-11-18 Update README.md
    Added BOM section for JLCPCB SMT assembly
2022-11-23 Updated JLC BOM in README.md
2022-11-23 Updated PCB layout for DZ65 compatibility.
2022-12-23 Updates in routed PCB.
2023-01-03 Initial routing completed. Need to clean up DRC and optimize board.
2023-01-03 Some DRC cleanup.
2023-01-03 Updated kicad_libs submodule to newest version.
2023-01-03 Updates on PCB, schematic and submodules.
2023-01-03 Updated ground polygon on PCB.
2023-01-04 Updates to the PCB and the schematic.
2023-01-04 Updated kicad_libs submodule.
2023-01-06 Added USB shield circuit to schematic and PCB.
2023-01-06 Updated routing of USB traces.
2023-01-06 Updated JLC part numbers in schematic.
2023-01-08 Updated PCB.
2023-01-11 Final design for initial JLCPCB production.
2023-01-13 Updated ground fill on PCB.
2023-01-13 Added BOM script for JLCPCB.
2023-02-17 Final design for first JLCPCB production run.
2023-02-26 Added KLE (keyboard layout editor) JSON file for kuro65 VIA configuration.
2023-03-14 Updated schematic pictures and product pictures.
